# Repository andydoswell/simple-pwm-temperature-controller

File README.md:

# simple-pwm-temperature-controller

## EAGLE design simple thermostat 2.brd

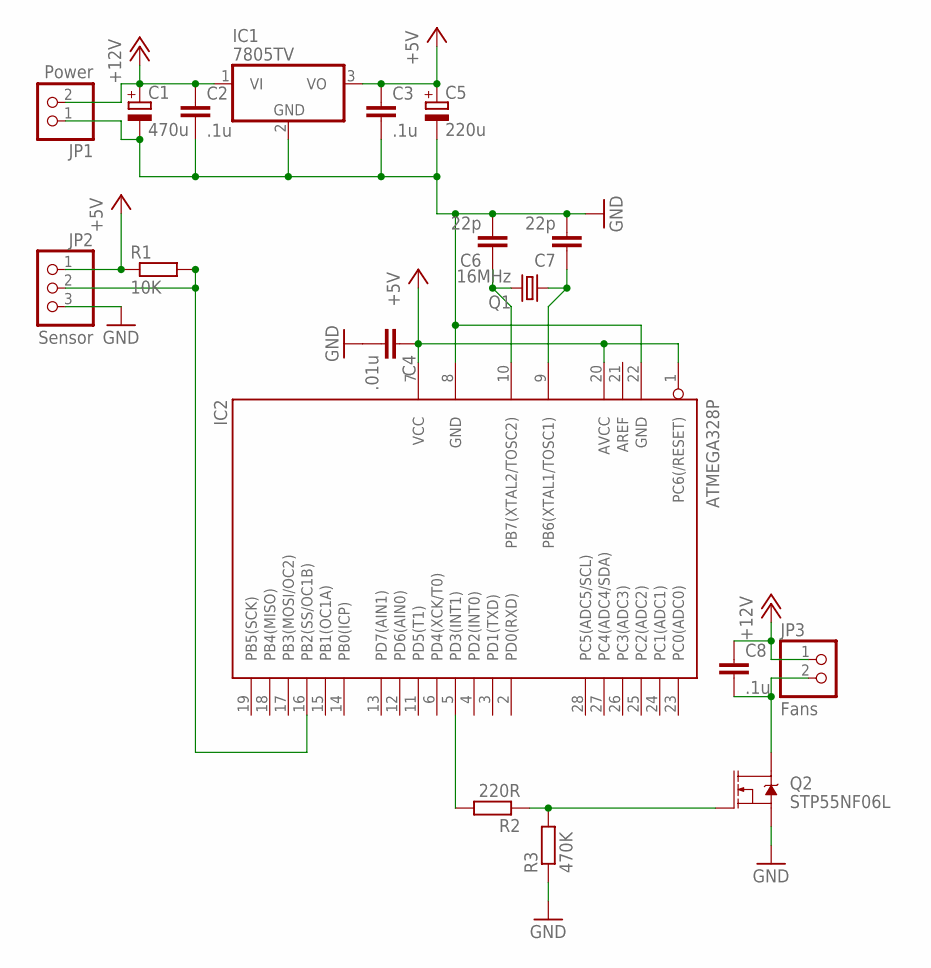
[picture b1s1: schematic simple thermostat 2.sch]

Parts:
C1: 470u; E3,5-10
C2, C3, C8: .1u; C025-024X044
C4: .01u; C025-024X044
C5: 220u; E2,5-7
C6, C7: 22p; C025-024X044
IC1: 7805TV; TO220V
IC2: ATMEGA328P; DIL28-3
JP1: Power; 1X02
JP2: Sensor; 1X03
JP3: Fans; 1X02
Q1: 16MHz; HC18U-V
Q2: STP55NF06L; TO220V
R1: 10K; 0207/7
R2: 220R; 0207/7
R3: 470K; 0207/7

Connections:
+5V: C3.1, C4.1, C5.+, IC1.3 (VO), IC2.1 (PC6(/RESET)), IC2.7 (VCC), IC2.20 (AVCC), JP2.1, R1.1
+12V: C1.+, C2.1, C8.1, IC1.1 (VI), JP1.2, JP3.1
GND: C1.-, C2.2, C3.2, C4.2, C5.-, C6.2, C7.2, IC1.2 (GND), IC2.8 (GND), IC2.22 (GND), JP1.1, JP2.3, Q2.3 (S), R3.1
unnamed: IC2.5 (PD3(INT1)), R2.2
unnamed: Q2.1 (G), R2.1, R3.2
unnamed: C8.2, JP3.2, Q2.2 (D)
unnamed: IC2.16 (PB2(SS/OC1B)), JP2.2, R1.2
unnamed: C7.1, IC2.9 (PB6(XTAL1/TOSC1)), Q1.1
unnamed: C6.1, IC2.10 (PB7(XTAL2/TOSC2)), Q1.2

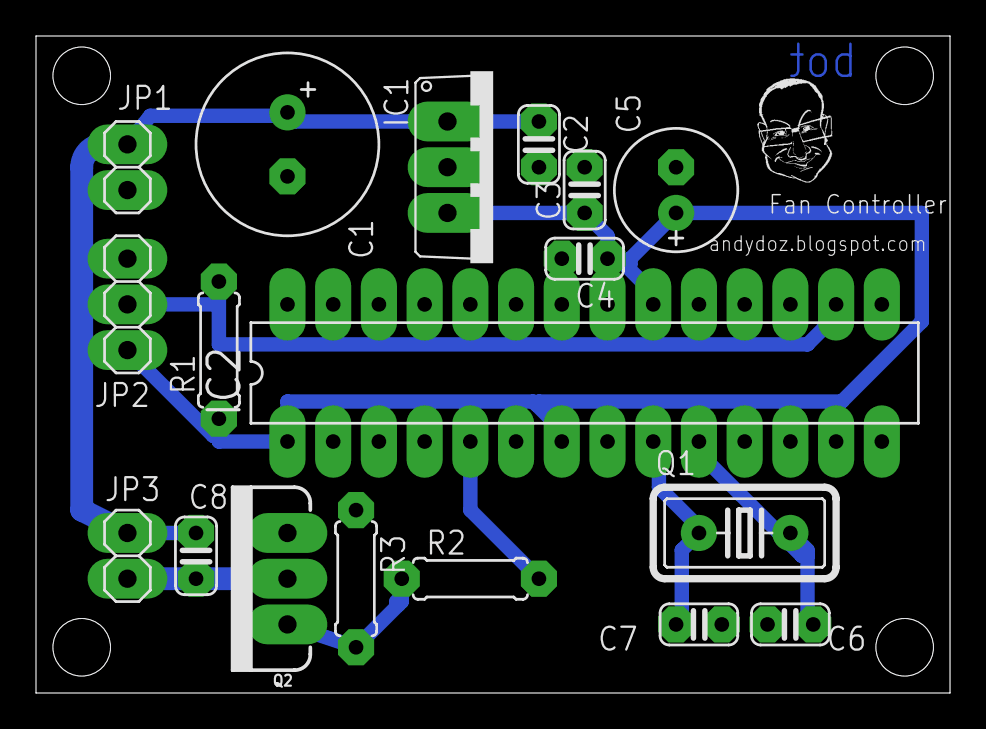
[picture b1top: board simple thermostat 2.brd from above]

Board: 2 copper layers, 50.8 x 36.5 mm, 18 parts (0 on the bottom side), 9 nets.

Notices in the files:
parts and their libraries:
SparkFun-DiscreteSemi: Licensing: Creative Commons ShareAlike 4.0 International - https://creativecommons.org/licenses/by-sa/4.0
